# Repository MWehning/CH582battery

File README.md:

# CH582battery
Board that employs the CH582 chip to read and transmit data from an IMU or other I2C Sensor. Full battery charge circuit and power supply

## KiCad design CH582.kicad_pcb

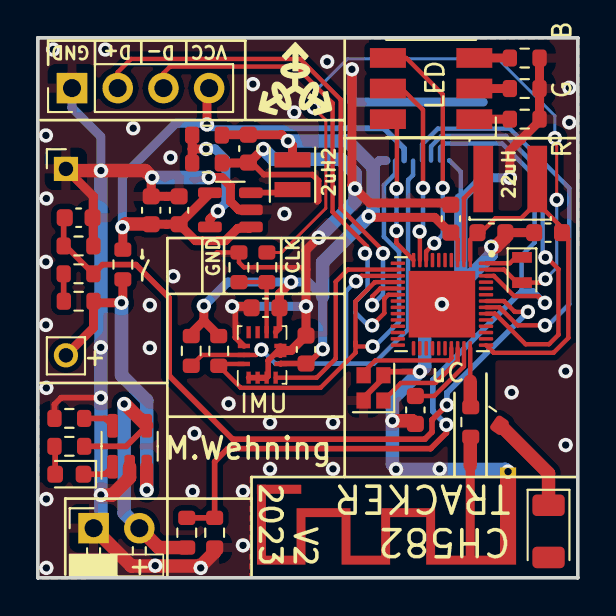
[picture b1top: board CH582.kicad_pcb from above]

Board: 2 copper layers, 30.0 x 30.0 mm, 45 parts (1 on the bottom side), 37 nets.

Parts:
AE1: Antenna_Shield; Texas_SWRA117D_2.4GHz_Right
AE2: Conn_01x01; Johanson_2450AT18x100
C1, C7, C8: 2.2uF; C_0603_1608Metric
C2, C3, C4: 100nF; C_0603_1608Metric
C5: 10uF; C_0603_1608Metric
C6, C9: 4.7uF; C_0603_1608Metric
C10: 10nF; C_0603_1608Metric
D1: Red; LED_0603_1608Metric
D3: LED_RGB; LED_RGB_5050-6
J1: Conn_01x02; PinHeader_1x02_P2.00mm_Vertical
J3: USB; PinHeader_1x04_P2.54mm_Vertical
J4: Conn_02x04_Odd_Even; Hirose_FH12-8S-0.5SH_1x08-1MP_P0.50mm_Horizontal
J5: Pogo Pin Socket 2.54; PinSocket_1x02_P2.54mm_Horizontal
L1: 22uH; L_Changjiang_FNR4020S
L2: 2.2uH; L_Changjiang_FNR252010S
R1, R4, R6: 10k; R_0603_1608Metric
R2: 300; R_0603_1608Metric
R3, R10: N.C.; R_0603_1608Metric
R5: 2k; R_0603_1608Metric
R7, R9, R14: 180; R_0603_1608Metric
R8: 0R; R_0603_1608Metric
R11: NC; R_0603_1608Metric
R12: 180k; R_0603_1608Metric
R13: 810k; R_0603_1608Metric
R15: 200k; R_0603_1608Metric
R16: ca. 100k; R_0603_1608Metric
R17: 100k; R_0603_1608Metric
R18: 0; R_0603_1608Metric
R19: 20k; R_0603_1608Metric
U1: Bosch_LGA-14_3x2.5mm_P0.5mm
U2: PJ4054B; SOT-23-5
U3: QFN 48 fixed
U4: M3406; SOT-23-5
Y1: 32MHz; Crystal_SMD_2016-4Pin_2.0x1.6mm
Y2: Crystal_Small; Crystal_SMD_2012-2Pin_2.0x1.2mm

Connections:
+3V3: C3.2, C4.2, C7.2, C9.2, J4.1, L2.2, R4.1, R6.1, R13.2, U1.5 (Vdd_IO), U1.8 (Vdd), U3.3 (VIO33/VDD33)
+5V: J5.2, R1.2, R2.2, U2.4 (VCC)
/B+: J1.2, R15.1, R18.2, U2.3 (BAT)
/DBG+: C5.2, C6.2, J3.4, J4.3, R18.1, U4.1 (RUN), U4.4 (VIN)
/PANT: AE2.1, R11.2
ADC: C10.1, R16.2, R17.1, U3.42 (PA3)
ANT: R8.2, R11.1, U3.34 (ANT)
DCA1: J4.6, U3.40 (PA1)
GND: AE1.2 (Shield), C1.1, C2.1, C3.1, C4.1, C5.1, C6.1, C7.1, C8.1, C9.1, C10.2, J1.1, J3.1, J4.8, J5.1, R3.1, R5.1, R7.1, R9.1, R12.1, R14.1, R17.2, R19.2, U1.1 (SDO/SA0), U1.2 (SDx/AH1/Qvar1), U1.3 (SCx/AH2/Qvar2), U1.6 (GND), U1.7 (GND), U1.12 (CS), U2.2 (GND), U3.0 (GND), U4.2 (GND), Y1.2, Y1.4
G_RST: J4.7, R1.1, R19.1, U3.46 (PA12/SCS)
ICM_CLK: R3.2, R10.1, U1.9 (INT2)
INT1: U1.4 (INT1), U3.12 (MOSI_)
INT2/DCA2: J4.5, U3.41 (PA2/TMR3_)
unnamed: AE1.1 (A), R8.1
unnamed: D1.2 (A), R2.1
unnamed: D1.1 (K), U2.1 (~CHRG)
unnamed: D3.4 (BA), U3.8 (PB8)
unnamed: D3.3 (BK), R7.2
unnamed: D3.5 (GA), U3.9 (PB17)
unnamed: D3.2 (GK), R9.2
unnamed: D3.6 (RA), U3.10 (PB16)
unnamed: D3.1 (RK), R14.2
unnamed: R15.2, R16.1
unnamed: R5.2, U2.5 (PROG)
unnamed: C1.2, U3.33 (VINTA)
unnamed: R12.2, R13.1, U4.5 (FB)
unnamed: L2.1, U4.3 (SW)
SCL: J4.4, R6.2, U1.13 (SCL), U3.13 (U2D+/SCL/TXD1)
SDA: J4.2, R4.2, U1.14 (SDA), U3.14 (U2D-/SDA/RXD1)
USB_D+: J3.2, U3.15 (UD+/TMR2)
USB_D-: J3.3, U3.16 (UD-/TMR1)
VDCIA: C2.2, C8.2, L1.2, U3.1 (VDCID), U3.35 (VDCIA)
VSW: L1.1, U3.2 (VSW)
X32KI: U3.48 (X32KI/TMR1), Y2.1
X32KO: R10.2, U3.47 (X32KO/TMR2), Y2.2
X32MI: U3.32 (X32MI), Y1.1
X32MO: U3.31 (X32MO), Y1.3

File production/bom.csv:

Designator,Footprint,Quantity,Value,LCSC Part #
AE1,Texas_SWRA117D_2.4GHz_Right,1,Antenna_Shield,
AE2,Johanson_2450AT18x100,1,Conn_01x01,
"C1, C7, C8",0603,3,2.2uF,
C10,0603,1,10nF,
"C2, C3, C4",0603,3,100nF,
C5,0603,1,10uF,
"C6, C9",0603,2,4.7uF,
D1,0603,1,Red,
D3,LED_RGB_5050-6,1,LED_RGB,
J1,PinHeader_1x02_P2.00mm_Vertical,1,Conn_01x02,
J3,PinHeader_1x04_P2.54mm_Vertical,1,USB,
J4,Hirose_FH12-8S-0.5SH_1x08-1MP_P0.50mm_Horizontal,1,Conn_02x04_Odd_Even,
J5,PinSocket_1x02_P2.54mm_Horizontal,1,Pogo Pin Socket 2.54,
L1,L_Changjiang_FNR4020S,1,22uH,
L2,L_Changjiang_FNR252010S,1,2.2uH,
"R1, R4, R6",0603,3,10k,
"R10, R3",0603,2,N.C.,
R11,0603,1,NC,
R12,0603,1,180k,
R13,0603,1,810k,
"R14, R7, R9",0603,3,180,
R15,0603,1,200k,
R16,0603,1,ca. 100k,
R17,0603,1,100k,
R18,0603,1,0,
R19,0603,1,20k,
R2,0603,1,300,
R5,0603,1,2k,
R8,0603,1,0R,
U1,Bosch_LGA-14_3x2.5mm_P0.5mm,1,~,
U2,SOT-23-5,1,PJ4054B,
U3,QFN 48 fixed,1,~,
U4,SOT-23-5,1,M3406,
Y1,Crystal_SMD_2016-4Pin_2.0x1.6mm,1,32MHz,
Y2,Crystal_SMD_2012-2Pin_2.0x1.2mm,1,Crystal_Small,

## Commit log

2023-08-04 added charging circuit
2023-08-04 restructured layout
2023-08-07 Bat Lvl, GP conn, icm/lsm
2023-08-07 added testpoints/pad reset
2023-08-08 added USB flashing interface, rgb led, mounting hole
2023-08-18 added pogo port and reset switch
2023-08-24 V1, aux not connected
2023-08-24 goodbye 0.1mm
2023-08-24 antenna tuning
2023-08-24 GROUND VIASgit add -A
2023-08-24 fixed clearance issues
2023-08-24 final tweaks 1
2023-08-24 added gitignore
2023-08-25 V1, order version
2023-08-25 tweaks3
